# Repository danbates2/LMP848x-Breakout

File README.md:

Free to use.

SHUNT MONITOR BREAKOUT BOARD FOR LMP8481 or similar chips.

openenergymonitor.org

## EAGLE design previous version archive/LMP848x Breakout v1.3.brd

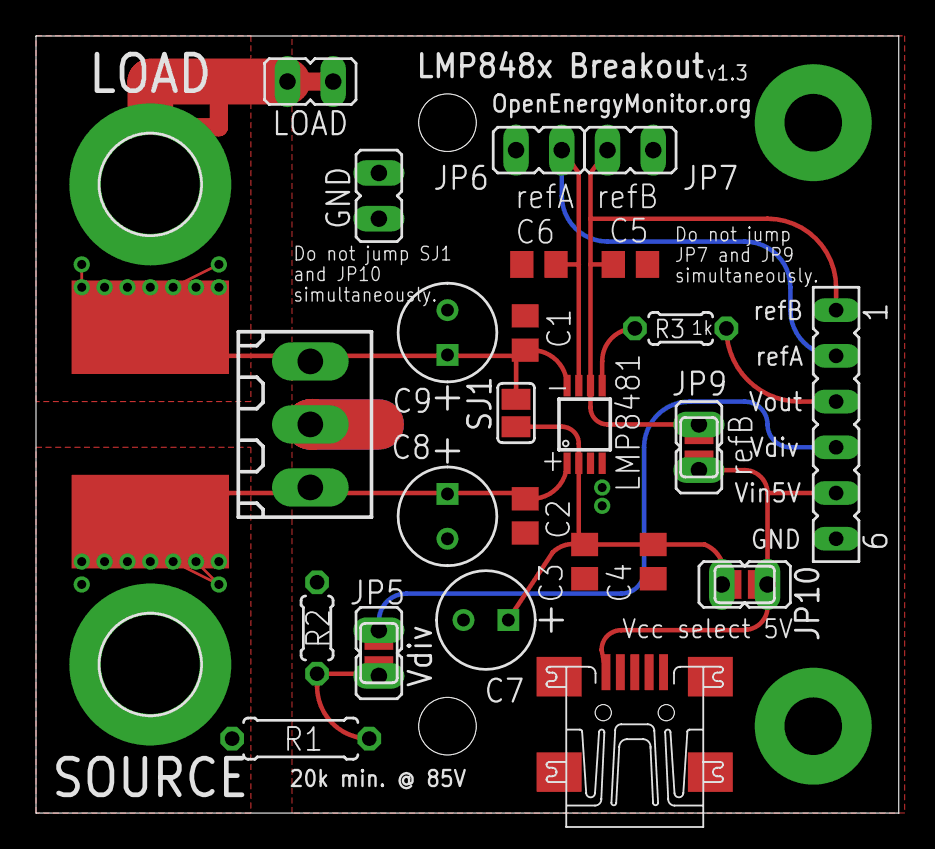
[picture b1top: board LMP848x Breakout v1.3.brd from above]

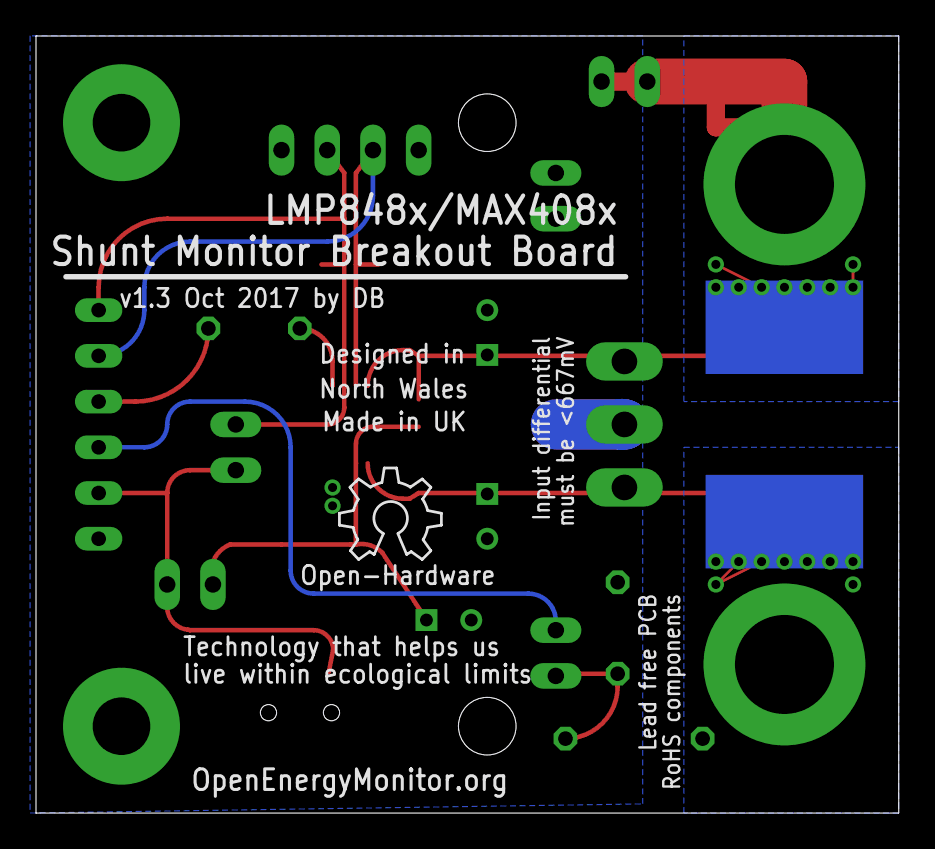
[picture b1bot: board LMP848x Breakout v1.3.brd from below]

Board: 2 copper layers, 47.9 x 43.2 mm, 32 parts (2 on the bottom side), 11 nets.

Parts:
C1, C2, C3: 100nF 100V; C0805
C4: 220nF 100V; C0805
C5, C6: 100nF 6V; C0805
C7, C8, C9: 10UF; CAPPR250-500X1100
GND: JP1
H3, H4: MOUNT-PAD-ROUND5.5; 5,5-PAD
JP5: Vdiv; JP1
JP6: refA; JP1
JP7: refB; JP1
JP9: refB to Vcc; JP1
JP10: Vcc select 5V; JP1
LMP8481: LMP8481-H; S-PDSO-G08
LOAD: JP1
LOGO1: OSHW_LOGO_6MILX0200-NT; OSHW_6X200_NOTEXT
R1: 100k; 0207/7
R2: 6.2k; 0204/5
R3: 1k; 0204/5
SCREW1: 180-3
SHUNT, SHUNT1: EBW_SERIES_15.2MM
SJ1, SJ2, SJ3, SJ4: SJ
SV1: FE06
X1: MINI-USB-UX60-MB-5ST; UX60-MB-5ST

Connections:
GND: C1.1, C2.2, C3.2, C4.2, C5.2, C6.2, C7.2, C8.2, C9.2, GND.1, GND.2, JP6.1, JP7.2, LMP8481.4, R2.1, SCREW1.2, SV1.6, X1.5
LOAD: C1.2, C9.1, H3.B5,5, LMP8481.8, LOAD.1, LOAD.2, SCREW1.1, SHUNT.P$2, SHUNT1.P$2, SJ1.2
unnamed: C3.1, C4.1, C7.1, JP10.1, LMP8481.2, SJ1.1, SJ3.2
unnamed: LMP8481.5, R3.1
unnamed: C5.1, JP7.1, JP9.1, LMP8481.6, SJ4.1, SV1.1
unnamed: JP9.2, JP10.2, SJ3.1, SJ4.2, SV1.5, X1.1
unnamed: R3.2, SV1.3
unnamed: C6.1, JP6.2, LMP8481.7, SV1.2
unnamed: JP5.1, R1.1, R2.2, SJ2.2
SOURCE: C2.1, C8.1, H4.B5,5, LMP8481.1, R1.2, SCREW1.3, SHUNT.P$1, SHUNT1.P$1
VDIV: JP5.2, SJ2.1, SV1.4

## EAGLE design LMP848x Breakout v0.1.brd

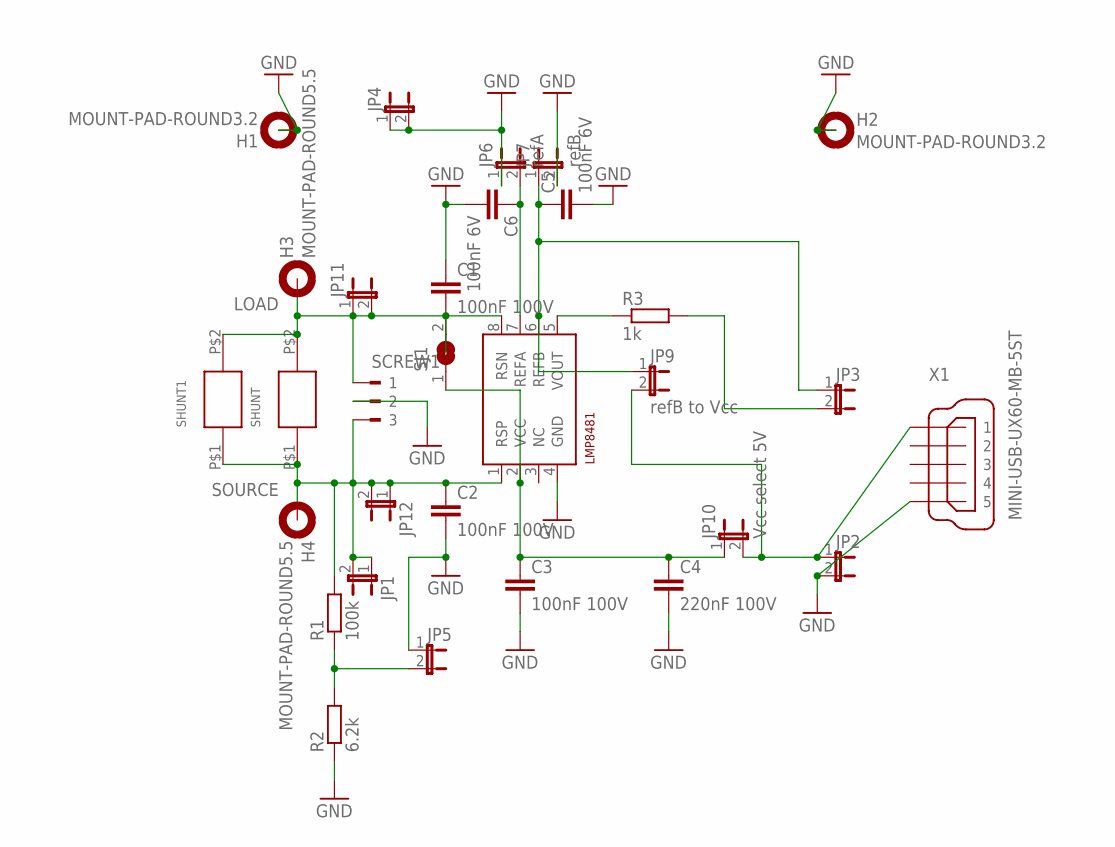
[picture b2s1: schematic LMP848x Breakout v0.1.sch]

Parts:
C1, C2, C3: 100nF 100V; C0805
C4: 220nF 100V; C0805
C5, C6: 100nF 6V; C0805
H1, H2: MOUNT-PAD-ROUND3.2; 3,2-PAD
H3, H4: MOUNT-PAD-ROUND5.5; 5,5-PAD
JP1, JP2, JP3, JP4, JP5, JP11, JP12: JP1E; JP1
JP6: refA; JP1
JP7: refB; JP1
JP9: refB to Vcc; JP1
JP10: Vcc select 5V; JP1
LMP8481: LMP8481-H; S-PDSO-G08
R1: 100k; 0207/7
R2: 6.2k; 0207/7
R3: 1k; 0204/5
SCREW1: 180-3
SHUNT, SHUNT1: EBW_SERIES_15.2MM
SJ1: SJ
X1: MINI-USB-UX60-MB-5ST; UX60-MB-5ST

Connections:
GND: C1.1, C2.2, C3.2, C4.2, C5.2, C6.2, H1.B3,2, H2.B3,2, JP2.2, JP4.1, JP4.2, JP5.1, JP6.1, JP7.2, LMP8481.4 (GND), R2.1, SCREW1.2, X1.5
LOAD: C1.2, H3.B5,5, JP11.1, JP11.2, LMP8481.8 (RSN), SCREW1.1, SHUNT.P$2, SHUNT1.P$2, SJ1.2
unnamed: C3.1, C4.1, JP10.1, LMP8481.2 (VCC), SJ1.1
unnamed: LMP8481.5 (VOUT), R3.1
unnamed: C5.1, JP3.1, JP7.1, JP9.1, LMP8481.6 (REFB)
unnamed: JP2.1, JP9.2, JP10.2, X1.1
unnamed: JP3.2, R3.2
unnamed: C6.1, JP6.2, LMP8481.7 (REFA)
SOURCE: C2.1, H4.B5,5, JP1.1, JP1.2, JP12.1, JP12.2, LMP8481.1 (RSP), R1.2, SCREW1.3, SHUNT.P$1, SHUNT1.P$1
VSENSE: JP5.2, R1.1, R2.2

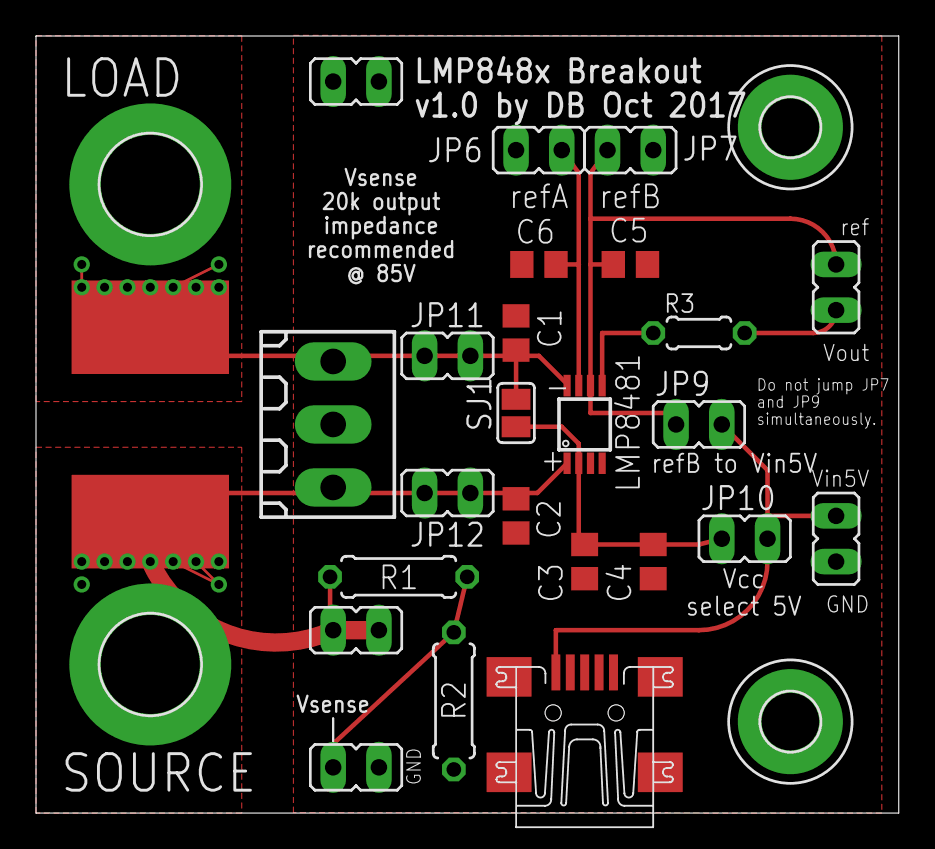
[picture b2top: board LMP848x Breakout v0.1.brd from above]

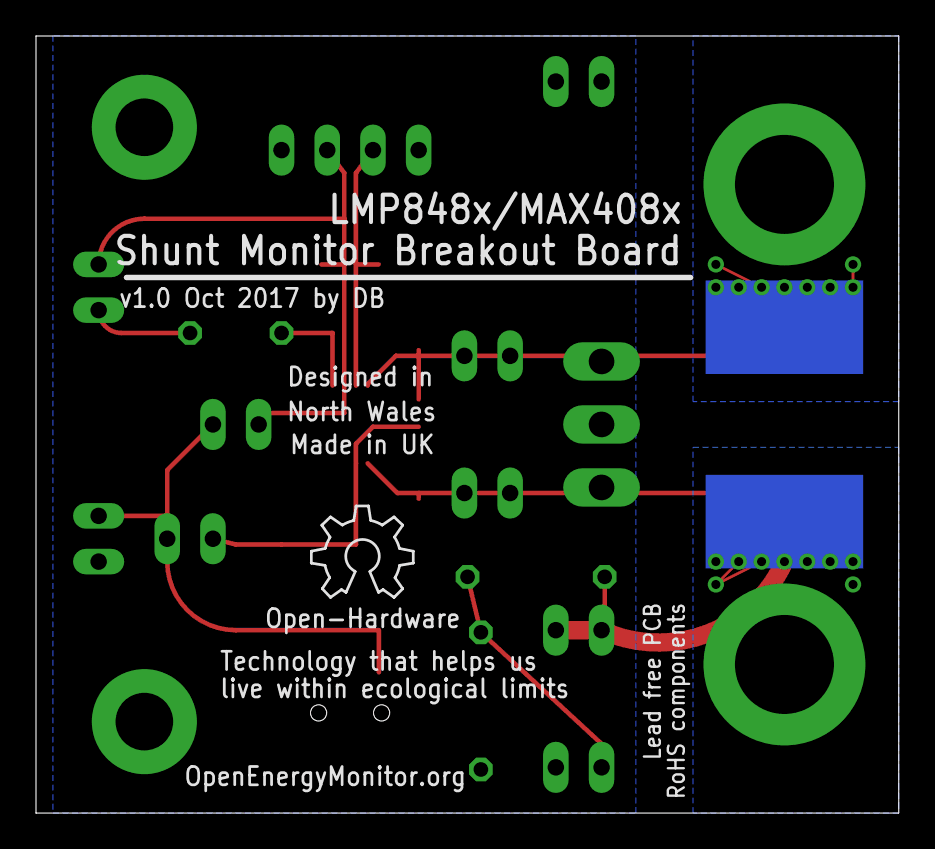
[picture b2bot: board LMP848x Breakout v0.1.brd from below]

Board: 2 copper layers, 47.9 x 43.2 mm, 31 parts (2 on the bottom side), 10 nets.

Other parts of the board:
LOGO1: OSHW_LOGO_6MILX0200-NT; OSHW_6X200_NOTEXT

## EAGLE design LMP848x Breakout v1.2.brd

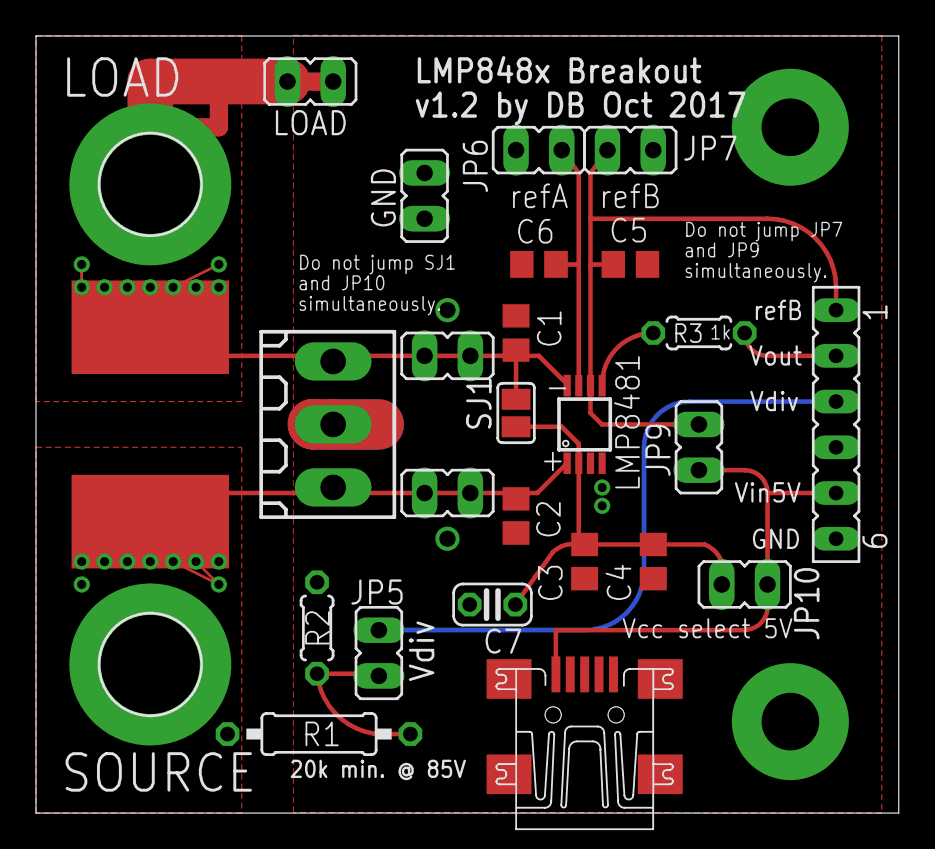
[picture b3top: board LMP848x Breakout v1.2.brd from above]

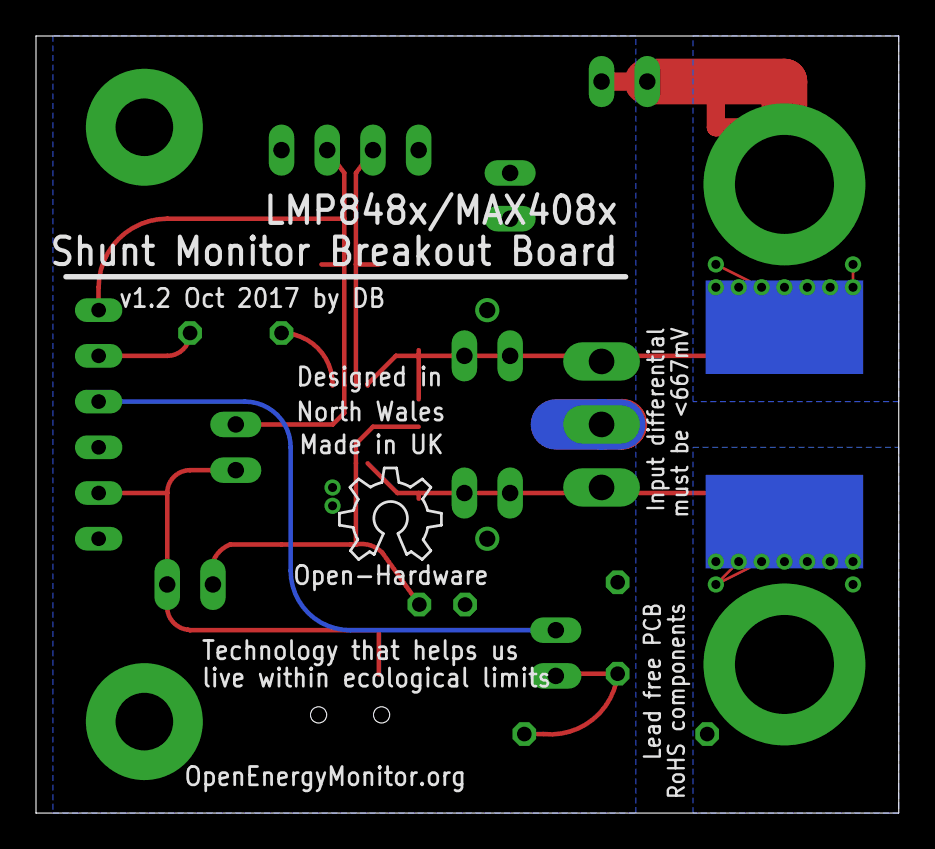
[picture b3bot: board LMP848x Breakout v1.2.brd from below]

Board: 2 copper layers, 47.9 x 43.2 mm, 29 parts (2 on the bottom side), 11 nets.

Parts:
C1, C2, C3: 100nF 100V; C0805
C4: 220nF 100V; C0805
C5, C6: 100nF 6V; C0805
C7: 10uF; C025-024X044
GND: JP1
H3, H4: MOUNT-PAD-ROUND5.5; 5,5-PAD
JP5: Vdiv; JP1
JP6: refA; JP1
JP7: refB; JP1
JP9: refB to Vcc; JP1
JP10: Vcc select 5V; JP1
JP11, JP12: JP1
LMP8481: LMP8481-H; S-PDSO-G08
LOAD: JP1
LOGO1: OSHW_LOGO_6MILX0200-NT; OSHW_6X200_NOTEXT
R1: 100k; 0207/10
R2: 6.2k; 0204/5
R3: 1k; 0204/5
SCREW1: 180-3
SHUNT, SHUNT1: EBW_SERIES_15.2MM
SJ1: SJ
SV1: FE06
X1: MINI-USB-UX60-MB-5ST; UX60-MB-5ST

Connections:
GND: C1.1, C2.2, C3.2, C4.2, C5.2, C6.2, C7.2, GND.1, GND.2, JP6.1, JP7.2, LMP8481.4, R2.1, SCREW1.2, SV1.6, X1.5
LOAD: C1.2, H3.B5,5, JP11.1, JP11.2, LMP8481.8, LOAD.1, LOAD.2, SCREW1.1, SHUNT.P$2, SHUNT1.P$2, SJ1.2
unnamed: C3.1, C4.1, C7.1, JP10.1, LMP8481.2, SJ1.1
unnamed: LMP8481.5, R3.1
unnamed: C5.1, JP7.1, JP9.1, LMP8481.6, SV1.1
unnamed: JP9.2, JP10.2, SV1.5, X1.1
unnamed: R3.2, SV1.2
unnamed: C6.1, JP6.2, LMP8481.7
unnamed: JP5.1, R1.1, R2.2
SOURCE: C2.1, H4.B5,5, JP12.1, JP12.2, LMP8481.1, R1.2, SCREW1.3, SHUNT.P$1, SHUNT1.P$1
VDIV: JP5.2, SV1.3

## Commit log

2017-10-12 v1.2 commit
2017-10-13 v1.3 commit
2017-10-13 v1.4 commit
